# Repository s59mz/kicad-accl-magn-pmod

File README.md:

# accl_magn_pmod
PMOD PCB module for ADXL345 Accelerometer and HMC5883L Magnetometer 

Schematic:
[accl_magn_pmod.pdf](accl_magn_pmod.pdf)

BOM:
[accl_magn_pmod.csv](accl_magn_pmod.csv)

Gerbers:
[gerbers.zip](https://github.com/s59mz/kicad-accl-magn-pmod/raw/main/gerbers.zip)

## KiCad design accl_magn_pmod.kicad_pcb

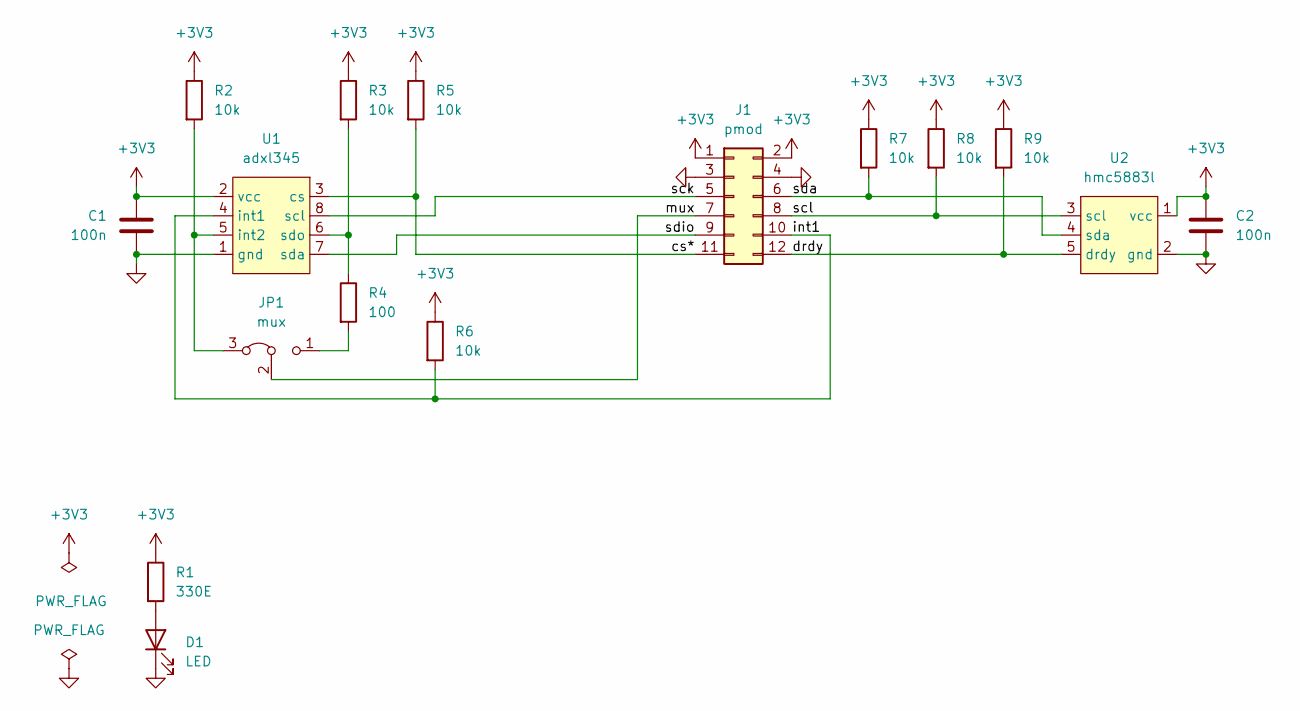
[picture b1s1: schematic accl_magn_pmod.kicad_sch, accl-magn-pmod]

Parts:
C1, C2: 100n; C_0603_1608Metric_Pad1.08x0.95mm_HandSolder
D1: LED; LED_0603_1608Metric_Pad1.05x0.95mm_HandSolder
J1: pmod; PinHeader_2x06_P2.54mm_Horizontal
JP1: mux; PinHeader_1x03_P2.54mm_Vertical
R1: 330E; R_0603_1608Metric_Pad0.98x0.95mm_HandSolder
R2, R3, R5, R6, R7, R8, R9: 10k; R_0603_1608Metric_Pad0.98x0.95mm_HandSolder
R4: 100; R_0603_1608Metric_Pad0.98x0.95mm_HandSolder
U1: adxl345
U2: hmc5883l

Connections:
+3V3: C1.1, C2.1, J1.1, J1.2, R1.1, R2.1, R3.1, R5.1, R6.1, R7.1, R8.1, R9.1, U1.2 (vcc), U2.1 (vcc)
/cs*: J1.11, R5.2, U1.3 (cs)
/drdy: J1.12, R9.2, U2.5 (drdy)
/int1: J1.10, R6.2, U1.4 (int1)
/mux: J1.7, JP1.2 (C)
/sck: J1.5, U1.8 (scl)
/scl: J1.8, R8.2, U2.3 (scl)
/sda: J1.6, R7.2, U2.4 (sda)
/sdio: J1.9, U1.7 (sda)
GND: C1.2, C2.2, D1.1 (K), J1.3, J1.4, U1.1 (gnd), U2.2 (gnd)
unnamed: D1.2 (A), R1.2
unnamed: JP1.1 (B), R4.2
unnamed: JP1.3 (A), R2.2, U1.5 (int2)
unnamed: R3.2, R4.1, U1.6 (sdo)

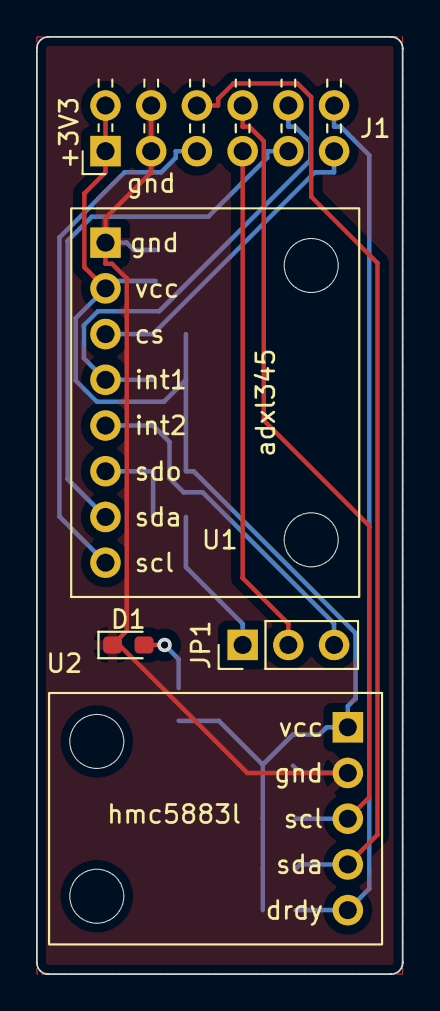
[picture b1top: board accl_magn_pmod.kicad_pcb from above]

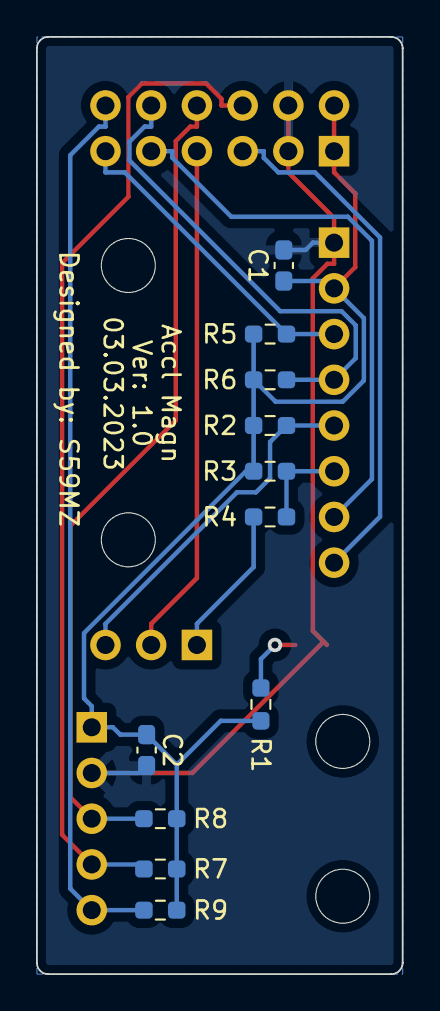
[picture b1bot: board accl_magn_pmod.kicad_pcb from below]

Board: 2 copper layers, 20.3 x 52.1 mm, 16 parts (11 on the bottom side), 14 nets.

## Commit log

2024-08-11 add screenshots
2024-08-11 updated bom
